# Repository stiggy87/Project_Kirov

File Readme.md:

Project Kirov is a hardware and software design project. The purpose of Project Kirov is to create a fully autonomous blimp to compete in the 2013 annual AVC held at Sparkfun in Boulder Colorado.

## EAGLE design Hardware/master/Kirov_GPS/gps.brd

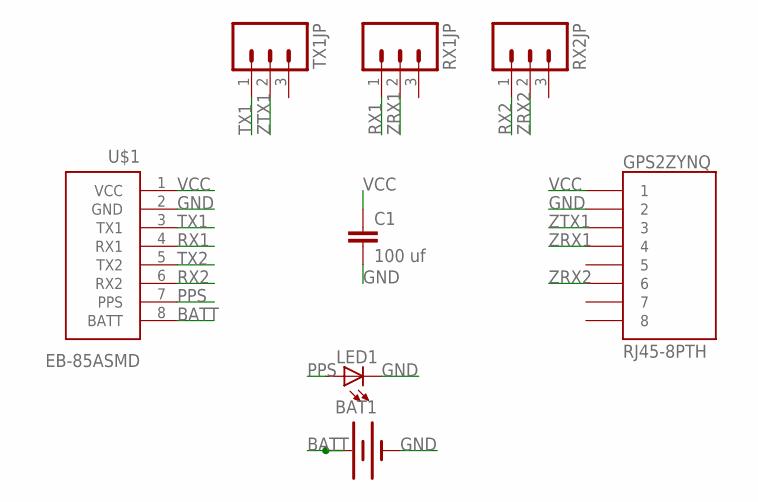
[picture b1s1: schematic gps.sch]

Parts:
BAT1: BATTERY12PTH; BATTCON_12MM_PTH
C1: 100 uf; CAP-PTH-5MM
GPS2ZYNQ: RJ45-8PTH; RJ45-8
LED1: LED5MM
RX1JP, RX2JP: M03LONGPADS; 1X03_LONGPADS
TX1JP: M03LONGPADS; 1X03_LONGPADS
U$1: EB-85ASMD; EB-85A

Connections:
BATT: BAT1.VCC@1 (+), U$1.8 (BATT)
GND: BAT1.GND (-), C1.2, GPS2ZYNQ.2, LED1.K (C), U$1.2 (GND)
PPS: LED1.A, U$1.7 (PPS)
RX1: RX1JP.1, U$1.4 (RX1)
RX2: RX2JP.1, U$1.6 (RX2)
TX1: TX1JP.1, U$1.3 (TX1)
TX2: U$1.5 (TX2)
VCC: C1.1, GPS2ZYNQ.1, U$1.1 (VCC)
ZRX1: GPS2ZYNQ.4, RX1JP.2
ZRX2: GPS2ZYNQ.6, RX2JP.2
ZTX1: GPS2ZYNQ.3, TX1JP.2

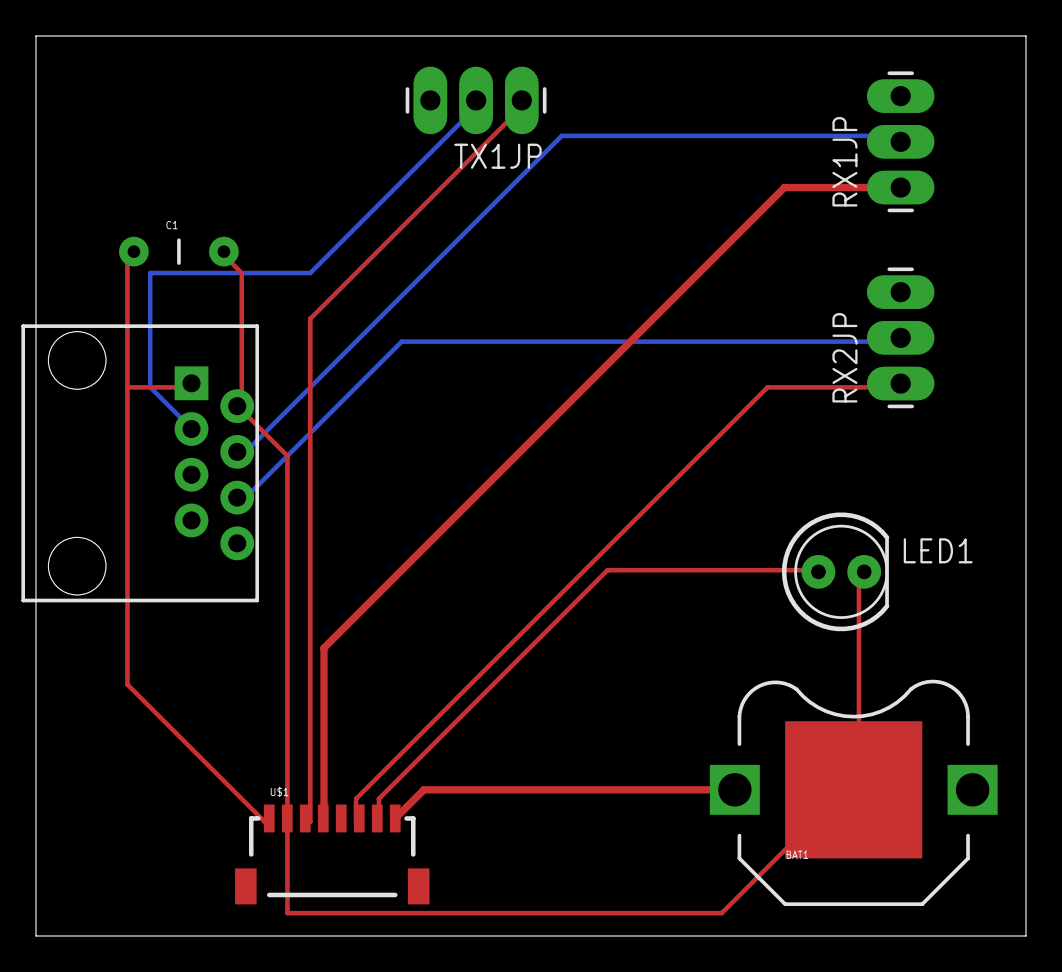
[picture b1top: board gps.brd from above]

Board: 2 copper layers, 55.0 x 50.0 mm, 8 parts (0 on the bottom side), 10 nets.

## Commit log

2012-08-14 Initial Publish
    Initial building of the Project Kirov Github repo
2012-08-14 Readme files for each separate branch
    The project has 3 main branches: Documentation, Hardware, Software. In
    Hardware and Software have 3 branches: master, stable, tag. The master
    is where all code/objects go, and stable is a commit of stable master
    code. Tag is for any forthcoming patches.
2012-08-14 Added a blurb to the main readme.
2012-08-18 Initial GPS Board/Schematic
    This is the "breakout" board for the GPS module. It uses RJ-45 to run
    cable to the Zedboard.
2012-08-20 added board layout and cap to schematic
2012-08-20 FMC Daughterboard Intial
    Initial upload of the custom FMC daughterboard.
2012-08-21 Updated zed_fmc for GND and VCC Nets
    Phase 1 of pinouts. Phase 2 will be identifying what pins are needed.
2012-08-21 Updated zed_fmc with nets
    This is partial commit.
2012-08-22 Initial Project Kirov Overview Documentation
2012-09-01 Create gh-pages branch via GitHub
2012-09-05 Fixed Spelling errors
2012-10-28 Datasheets and BoM Upload
    These are the first datasheets for GPS, and Ultrasonic Range Finder.
    Zedboad datasheets at www.zedboard.org.

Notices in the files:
parts and their libraries:
SparkFun-Connectors: Licensing: CC v3.0 Share-Alike You are welcome to use this library for commercial purposes.
